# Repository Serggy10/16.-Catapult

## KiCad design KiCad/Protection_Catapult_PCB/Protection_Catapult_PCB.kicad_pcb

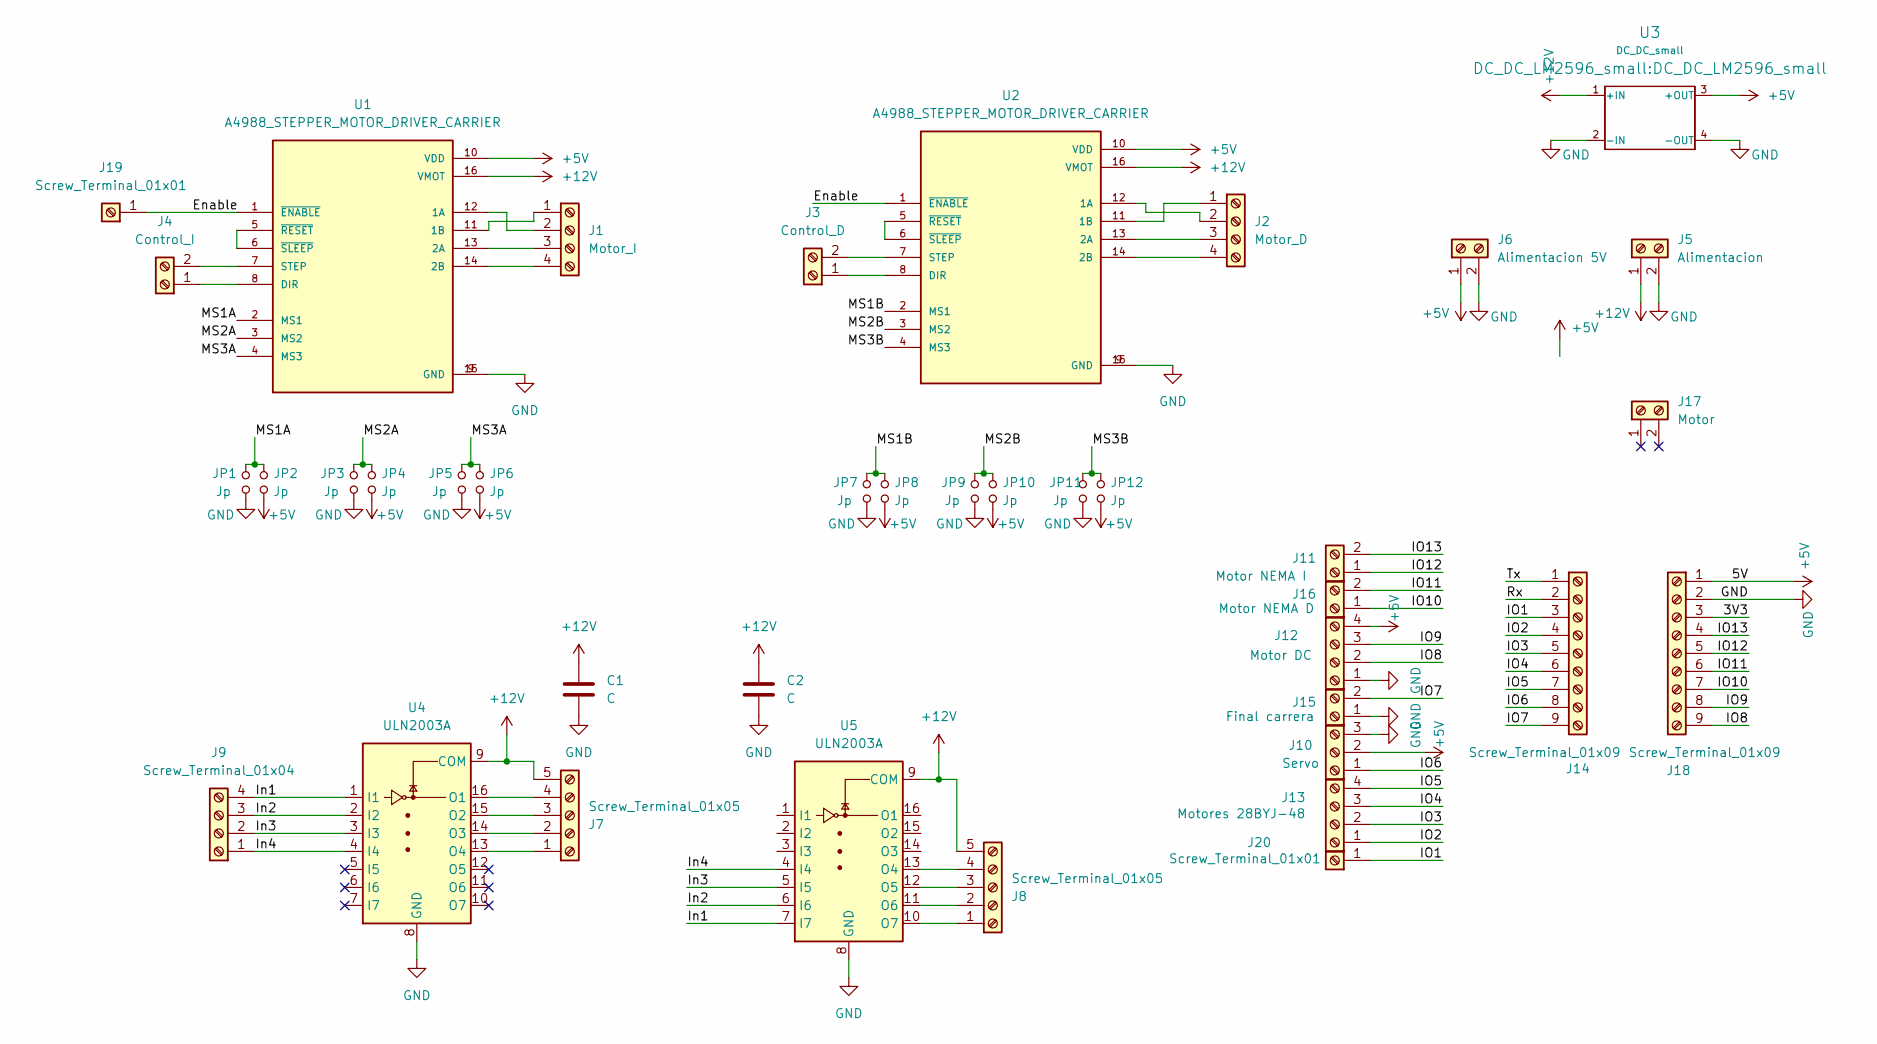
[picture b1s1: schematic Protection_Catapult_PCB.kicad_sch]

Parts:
C1, C2: C; C_Disc_D4.3mm_W1.9mm_P5.00mm
J1: Motor_I; JST_XH_B4B-XH-A_1x04_P2.50mm_Vertical
J2: Motor_D; JST_XH_B4B-XH-A_1x04_P2.50mm_Vertical
J3: Control_D; JST_XH_B2B-XH-A_1x02_P2.50mm_Vertical
J4: Control_I; JST_XH_B2B-XH-A_1x02_P2.50mm_Vertical
J5: Alimentacion; TerminalBlock_Pheonix_MPT-2.54mm_2pol
J6: Alimentacion 5V; TerminalBlock_Pheonix_MPT-2.54mm_2pol
J7, J8: Screw_Terminal_01x05; JST_XH_B5B-XH-A_1x05_P2.50mm_Vertical
J9: Screw_Terminal_01x04; JST_XH_B4B-XH-A_1x04_P2.50mm_Vertical
J10: Servo; JST_XH_B3B-XH-A_1x03_P2.50mm_Vertical
J11: Motor NEMA I; JST_XH_B2B-XH-A_1x02_P2.50mm_Vertical
J12: Motor DC; JST_XH_B4B-XH-A_1x04_P2.50mm_Vertical
J13: Motores 28BYJ-48; JST_XH_B4B-XH-A_1x04_P2.50mm_Vertical
J14, J18: Screw_Terminal_01x09; PinHeader_1x09_P2.54mm_Vertical
J15: Final carrera; JST_XH_B2B-XH-A_1x02_P2.50mm_Vertical
J16: Motor NEMA D; JST_XH_B2B-XH-A_1x02_P2.50mm_Vertical
J17: Motor; JST_XH_B2B-XH-A_1x02_P2.50mm_Vertical
J19, J20: Screw_Terminal_01x01; PinHeader_1x01_P2.54mm_Vertical
JP1, JP2, JP3, JP4, JP5, JP6, JP7, JP8, JP9, JP10, JP11, JP12: Jp; Pin_Header_Straight_1x02_Pitch2.54mm
U1, U2: A4988_STEPPER_MOTOR_DRIVER_CARRIER; MODULE_A4988_STEPPER_MOTOR_DRIVER_CARRIER
U3: DC_DC_small; DC_DC_LM2596_small
U4, U5: ULN2003A; CERDIP-16_W7.62mm_SideBrazed

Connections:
+5V: J6.1, J10.2, J12.4, J18.1, JP2.1, JP4.1, JP6.1, JP8.1, JP10.1, JP12.1, U1.10 (VDD), U2.10 (VDD), U3.3 (+OUT)
+12V: C1.2, C2.2, J5.1, J7.5, J8.5, U1.16 (VMOT), U2.16 (VMOT), U3.1 (+IN), U4.9 (COM), U5.9 (COM)
/3V3: J18.3
/Enable: J19.1, U1.1 (~ENABLE), U2.1 (~ENABLE)
/IO1: J14.3, J20.1
/IO2: J13.1, J14.4
/IO3: J13.2, J14.5
/IO4: J13.3, J14.6
/IO5: J13.4, J14.7
/IO6: J10.1, J14.8
/IO7: J14.9, J15.2
/IO8: J12.2, J18.9
/IO9: J12.3, J18.8
/IO10: J16.1, J18.7
/IO11: J16.2, J18.6
/IO12: J11.1, J18.5
/IO13: J11.2, J18.4
/In1: J9.4, U4.1 (I1), U5.7 (I7)
/In2: J9.3, U4.2 (I2), U5.6 (I6)
/In3: J9.2, U4.3 (I3), U5.5 (I5)
/In4: J9.1, U4.4 (I4), U5.4 (I4)
/MS1A: JP1.2, JP2.2, U1.2 (MS1)
/MS1B: JP7.2, JP8.2, U2.2 (MS1)
/MS2A: JP3.2, JP4.2, U1.3 (MS2)
/MS2B: JP9.2, JP10.2, U2.3 (MS2)
/MS3A: JP5.2, JP6.2, U1.4 (MS3)
/MS3B: JP11.2, JP12.2, U2.4 (MS3)
/Rx: J14.2
/Tx: J14.1
GND: C1.1, C2.1, J5.2, J6.2, J10.3, J12.1, J15.1, J18.2, JP1.1, JP3.1, JP5.1, JP7.1, JP9.1, JP11.1, U1.9 (GND), U1.15 (GND), U2.9 (GND), U2.15 (GND), U3.2 (-IN), U3.4 (-OUT), U4.8 (GND), U5.8 (GND)
unnamed: J1.1, U1.11 (1B)
unnamed: J1.2, U1.12 (1A)
unnamed: J1.3, U1.13 (2A)
unnamed: J1.4, U1.14 (2B)
unnamed: J2.1, U2.11 (1B)
unnamed: J2.2, U2.12 (1A)
unnamed: J2.3, U2.13 (2A)
unnamed: J2.4, U2.14 (2B)
unnamed: J3.1, U2.8 (DIR)
unnamed: J3.2, U2.7 (STEP)
unnamed: J4.1, U1.8 (DIR)
unnamed: J4.2, U1.7 (STEP)
unnamed: J7.1, U4.13 (O4)
unnamed: J7.2, U4.14 (O3)
unnamed: J7.3, U4.15 (O2)
unnamed: J7.4, U4.16 (O1)
unnamed: J8.1, U5.10 (O7)
unnamed: J8.2, U5.11 (O6)
unnamed: J8.3, U5.12 (O5)
unnamed: J8.4, U5.13 (O4)
unnamed: U1.5 (~RESET), U1.6 (~SLEEP)
unnamed: U2.5 (~RESET), U2.6 (~SLEEP)

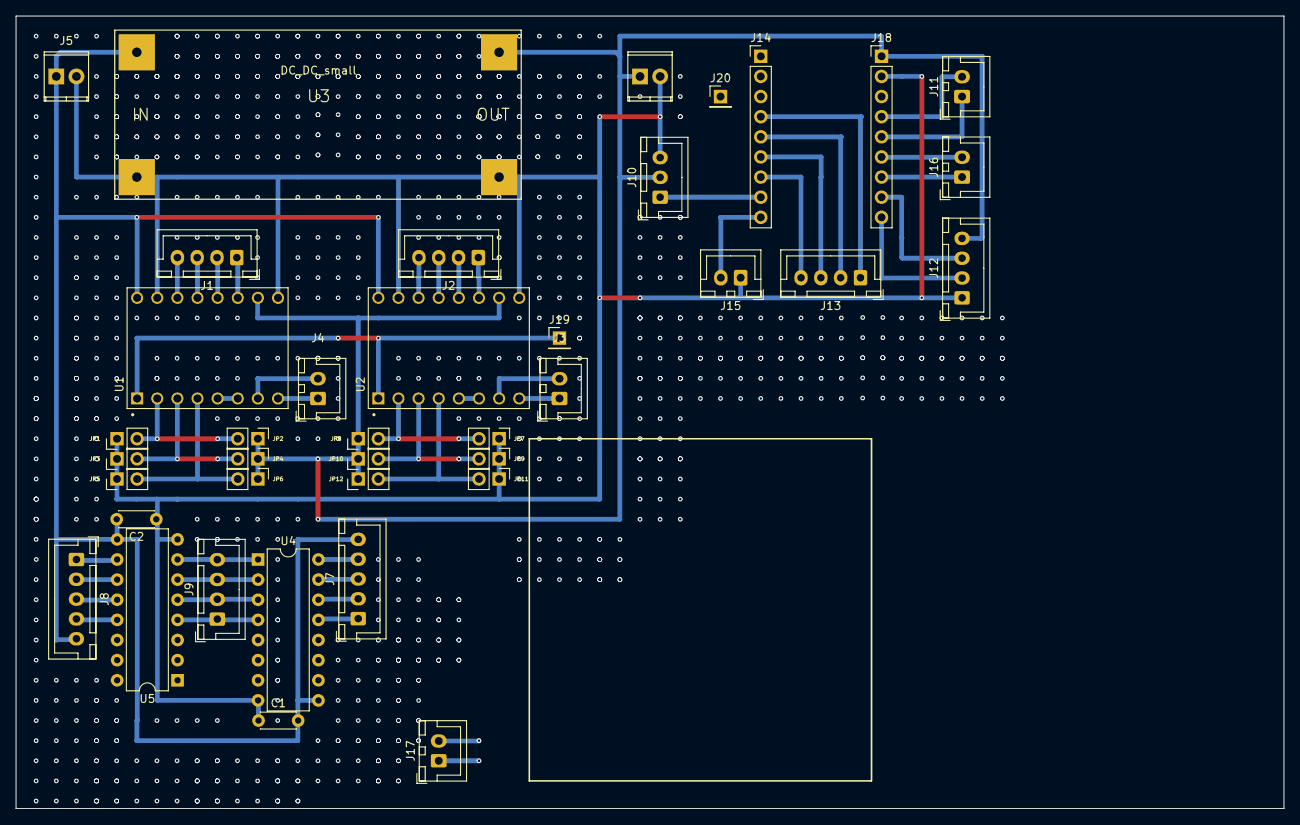
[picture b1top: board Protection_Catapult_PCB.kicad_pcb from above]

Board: 2 copper layers, 160.0 x 100.0 mm, 39 parts (0 on the bottom side), 49 nets.

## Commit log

2025-03-06 Initial commit.
2025-03-07 PCB Update.
2025-03-07 Test of 28BYJ-48 and servo. Brazo Catapulta model update.
2025-03-08 Inventor and PCB Update. Full program started.
2025-03-09 NEMA 17 supports added.
2025-03-11 Enable for A4988 PCB update toi disconect the motors.
2025-03-15 Full test of electronics. Functional program without Alexa.
2025-03-15 Code update
2025-03-16 Program and PCB update. Included alexa control by using Sinric Pro service.
